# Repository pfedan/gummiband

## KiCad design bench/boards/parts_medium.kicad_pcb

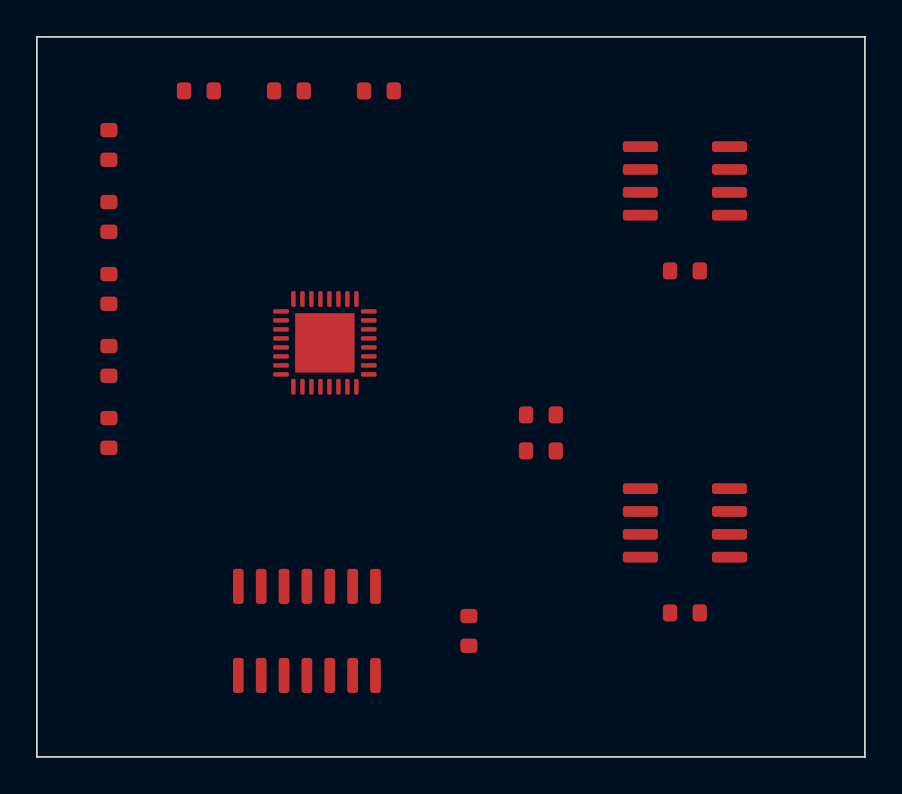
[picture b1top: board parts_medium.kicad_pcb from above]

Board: 2 copper layers, 46.0 x 40.0 mm, 17 parts (0 on the bottom side), 24 nets, no tracks yet.

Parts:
C1, C2, C3: 100n; C_0603
R1, R2: 4k7; R_0603
R3, R4, R5, R6, R7, R8, R9, R10: 10k; R_0603
U1: MCU; QFN-32
U2: Flash; SOIC-8
U3: Sensor; SOIC-8
U4: Latch; SOIC-14

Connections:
+3V3: C1.1, C2.1, C3.1, R1.1, R2.1, U1.25, U2.8, U3.8, U4.14
CS: U1.24, U2.1
GND: C1.2, C2.2, C3.2, U1.33, U2.4, U3.4, U4.7
INT: U1.19, U3.3
MISO: U1.23, U2.2
MOSI: U1.22, U2.5
N1: R5.1, U1.3
N2: R4.1, R6.1
N3: R6.2, R7.2
N4: R5.2, R9.1, U1.4
N5: R3.1, R9.2, U1.8
N6: R8.2, R10.2, U1.28
N7: R4.2, U1.5
N8: R3.2, R8.1, U1.1
N9: R7.1, R10.1, U1.29
Q0: U1.10, U4.13
Q1: U1.11, U4.12
Q2: U1.13, U4.10
Q3: U1.12, U4.11
Q4: U1.14, U4.9
Q5: U1.15, U4.8
SCK: U1.21, U2.6
SCL: R2.2, U1.17, U3.2
SDA: R1.2, U1.18, U3.1

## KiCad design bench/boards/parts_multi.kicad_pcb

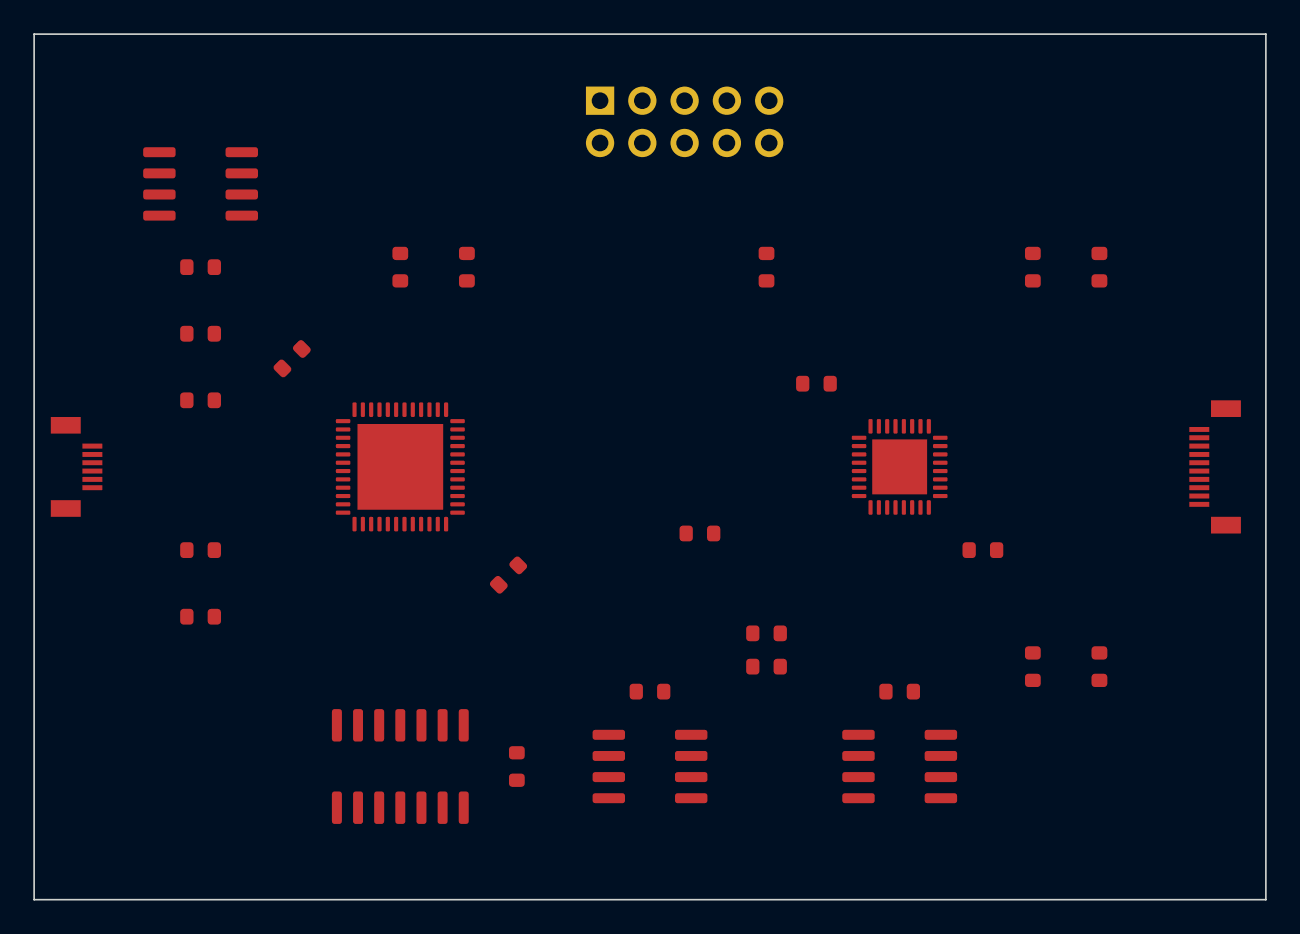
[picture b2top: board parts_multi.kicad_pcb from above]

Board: 4 copper layers, 74.0 x 52.0 mm, 31 parts (0 on the bottom side), 61 nets, no tracks yet.

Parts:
C1, C2, C3, C4, C5, C6, C7, C8: 100n; C_0603
J1: FPC; FPC-6P-0.5mm
J2: FPC; FPC-10P-0.5mm
J3: Conn; PinHeader_2x05
R1, R2: 4k7; R_0603
R3, R4, R5, R6, R7, R8, R9, R10, R11, R12, R13, R14: 10k; R_0603
U1: MCU; QFN-48
U2: MCU; QFN-32
U3: Flash; SOIC-8
U4: Latch; SOIC-14
U5: EEPROM; SOIC-8
U6: Sensor; SOIC-8

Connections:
+3V3: C1.1, C2.1, C3.1, C4.1, C5.1, C6.1, C7.1, C8.1, J3.8, R1.1, R2.1, U1.6, U1.30, U2.1, U3.8, U4.14, U5.8, U6.8
A0: U1.36, U2.2
A1: U1.35, U2.3
A2: U1.34, U2.4
A3: U1.33, U2.5
A4: U1.31, U2.7
A5: U1.32, U2.6
A6: U1.29, U2.8
A7: U1.28, U2.9
CS: U1.25, U2.12
F_CS: U1.46, U3.1
F_MISO: U1.45, U3.2
F_MOSI: U1.44, U3.5
F_SCK: U1.43, U3.6
GND: C1.2, C2.2, C3.2, C4.2, C5.2, C6.2, C7.2, C8.2, J1.1, J1.6, J2.1, J2.4, J2.7, J2.10, J3.6, J3.10, U1.7, U1.49, U2.32, U2.33, U3.4, U4.7, U5.4, U6.4
LED0: J2.5, U2.22
LED1: J2.6, U2.21
N1: R11.2, R12.2
N2: R3.2, R4.2, U1.1
N3: R7.1, R7.2, R8.1
N4: R3.1, R8.2, U3.7
N5: R5.1, U1.42
N6: R4.1, U1.8
N7: R13.2, U2.30, U2.31
N8: R14.1, U1.24, U2.29
N9: R10.2, U2.18
N10: R6.2, U1.13, U4.3
N11: R13.1, U2.13
N12: U1.12, U4.1
N13: R11.1, U2.17
N14: U1.20, U4.5
N15: R14.2, U1.23
N16: U1.38, U3.3
N17: R9.2, R10.1, R12.1
N18: R5.2, R6.1
N19: R9.1, U1.10, U4.4
N20: U1.37, U4.2, U4.6
NRST: J3.5, U1.41
Q0: U1.14, U4.13
Q1: U1.16, U4.11
Q2: U1.15, U4.12
Q3: U1.17, U4.10
Q4: U1.18, U4.9
Q5: U1.19, U4.8
RD: U1.26, U2.11
RX_N: J2.9, U2.19
RX_P: J2.8, U2.20
SCL: R2.2, U1.22, U2.16, U5.6, U6.6
SDA: R1.2, U1.21, U2.15, U5.5, U6.5
SWCLK: J3.3, U1.40
SWDIO: J3.1, U1.39
S_INT: U2.14, U6.1
TCK: J3.9, U2.27
TDI: J3.2, U2.26
TDO: J3.4, U2.25
TMS: J3.7, U2.28
TX_N: J2.3, U2.23
TX_P: J2.2, U2.24
USB_N: J1.3, U1.5
USB_P: J1.4, U1.4
WR: U1.27, U2.10

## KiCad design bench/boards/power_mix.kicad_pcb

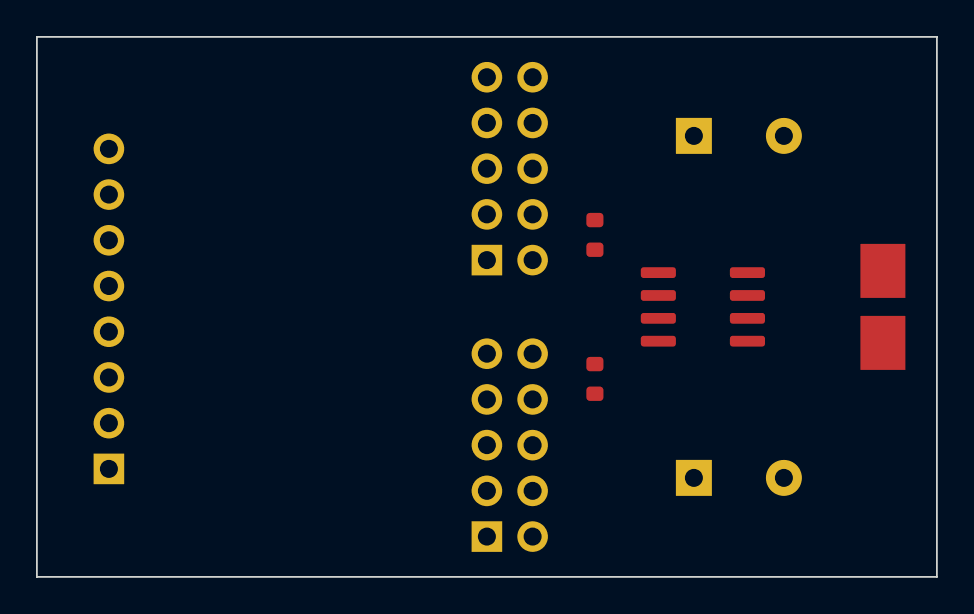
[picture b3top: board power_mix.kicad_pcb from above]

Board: 2 copper layers, 50.0 x 30.0 mm, 9 parts (0 on the bottom side), 7 nets, no tracks yet.

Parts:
C1, C2: 470u; CP_Radial_D8.0mm_P5.00mm
J1: Conn; PinHeader_1x08
J2: Load; PowerTab_2P
J3, J4: NC; PinHeader_2x05
R1, R2: 10k; R_0603
U1: Buck; SOIC-8

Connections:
GND: C1.2, C2.2, J1.3, J1.4, J2.2, R1.2, R2.2, U1.4
S1: J1.5, R1.1, U1.2
S2: J1.6, R2.1, U1.3
S3: J1.7, U1.5
S4: J1.8, U1.6
VIN: C1.1, J1.1, J1.2, U1.1, U1.8
VOUT: C2.1, J2.1, U1.7

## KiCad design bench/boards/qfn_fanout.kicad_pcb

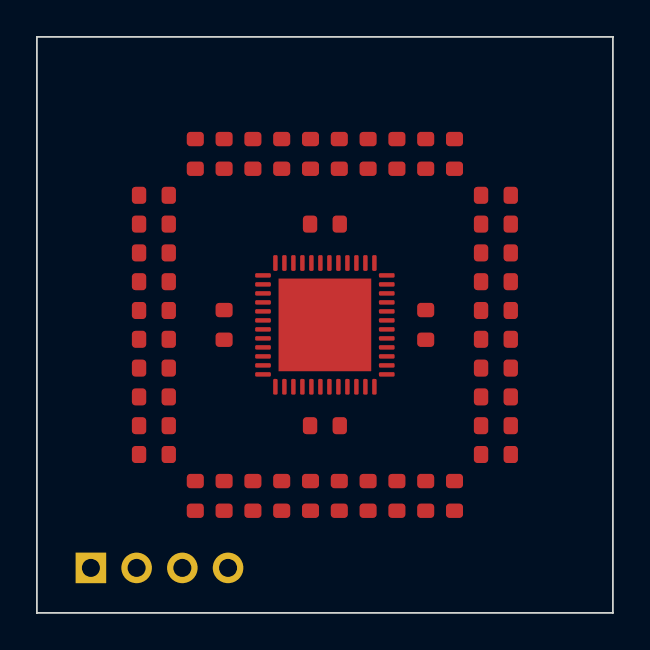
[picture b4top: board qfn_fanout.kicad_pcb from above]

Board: 4 copper layers, 32.0 x 32.0 mm, 46 parts (0 on the bottom side), 44 nets, no tracks yet.

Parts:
C1, C2, C3, C4: 100n; C_0603
J1: Conn; PinHeader_1x04
R1, R2, R3, R4, R5, R6, R7, R8, R9, R10, R11, R12, R13, R14, R15, R16, R17, R18, R19, R20, R21, R22, R23, R24, R25, R26, R27, R28, R29, R30, R31, R32, R33, R34, R35, R36, R37, R38, R39, R40: 10k; R_0603
U1: MCU; QFN-48

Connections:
+3V3: C1.1, C2.1, C3.1, C4.1, J1.2, R2.2, R4.2, R6.2, R8.2, R10.2, R12.2, R14.2, R16.2, R18.2, R20.2, R22.2, R24.2, R26.2, R28.2, R30.2, R32.2, R34.2, R36.2, R38.2, R40.2, U1.6, U1.18, U1.30, U1.42
GND: C1.2, C2.2, C3.2, C4.2, J1.1, R1.2, R3.2, R5.2, R7.2, R9.2, R15.2, R17.2, R19.2, R21.2, R23.2, R25.2, R27.2, R29.2, R31.2, R33.2, R35.2, R37.2, R39.2, U1.7, U1.19, U1.31, U1.43, U1.49
RX: J1.4, R13.2
S1: R1.1, U1.1
S2: R2.1, U1.2
S3: R3.1, U1.3
S4: R4.1, U1.4
S5: R5.1, U1.5
S6: R6.1, U1.8
S7: R7.1, U1.9
S8: R8.1, U1.10
S9: R9.1, U1.11
S10: R10.1, U1.12
S11: R11.1, U1.13
S12: R12.1, U1.14
S13: R13.1, U1.15
S14: R14.1, U1.16
S15: R15.1, U1.17
S16: R16.1, U1.20
S17: R17.1, U1.21
S18: R18.1, U1.22
S19: R19.1, U1.23
S20: R20.1, U1.24
S21: R21.1, U1.36
S22: R22.1, U1.35
S23: R23.1, U1.34
S24: R24.1, U1.33
S25: R25.1, U1.32
S26: R26.1, U1.29
S27: R27.1, U1.28
S28: R28.1, U1.27
S29: R29.1, U1.26
S30: R30.1, U1.25
S31: R31.1, U1.48
S32: R32.1, U1.47
S33: R33.1, U1.46
S34: R34.1, U1.45
S35: R35.1, U1.44
S36: R36.1, U1.41
S37: R37.1, U1.40
S38: R38.1, U1.39
S39: R39.1, U1.38
S40: R40.1, U1.37
TX: J1.3, R11.2

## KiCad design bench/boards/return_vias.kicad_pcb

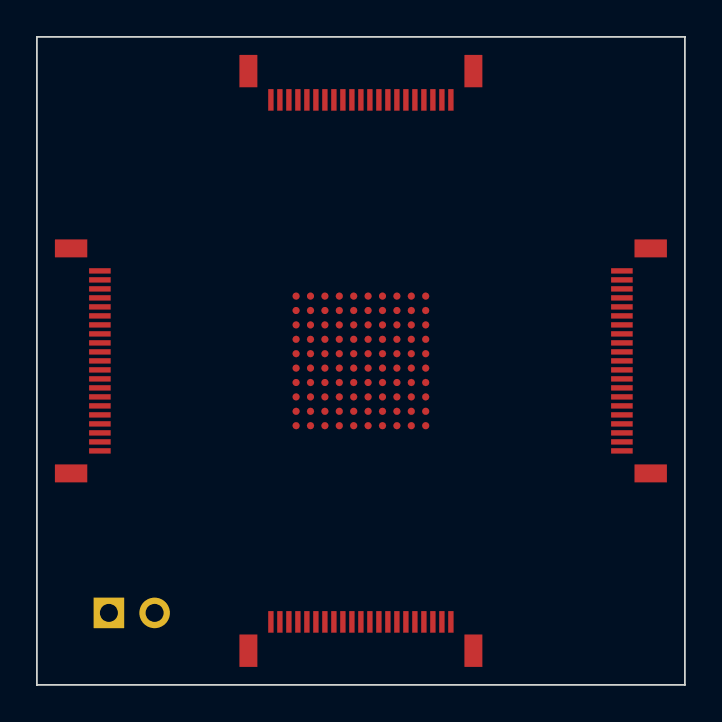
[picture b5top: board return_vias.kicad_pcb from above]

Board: 6 copper layers, 36.0 x 36.0 mm, 6 parts (0 on the bottom side), 85 nets, no tracks yet.

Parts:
J1, J2, J3, J4: FPC; FPC-21P-0.5mm
J5: Conn; PinHeader_1x02
U1: FPGA; BGA-100

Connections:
B0_0: J1.1, U1.A1
B0_1: J1.2, U1.A2
B0_2: J1.3, U1.B2
B0_3: J1.4, U1.A3
B0_4: J1.5, U1.B3
B0_5: J1.6, U1.C3
B0_6: J1.7, U1.A4
B0_7: J1.8, U1.B4
B0_8: J1.9, U1.C4
B0_9: J1.10, U1.A5
B0_10: J1.11, U1.B5
B0_11: J1.12, U1.C5
B0_12: J1.13, U1.A6
B0_13: J1.14, U1.B6
B0_14: J1.15, U1.C6
B0_15: J1.16, U1.A7
B0_16: J1.17, U1.B7
B0_17: J1.18, U1.C7
B0_18: J1.19, U1.A8
B0_19: J1.20, U1.B8
B0_20: J1.21, U1.A9
B1_0: J2.1, U1.A10
B1_1: J2.2, U1.B10
B1_2: J2.3, U1.B9
B1_3: J2.4, U1.C10
B1_4: J2.5, U1.C9
B1_5: J2.6, U1.C8
B1_6: J2.7, U1.D10
B1_7: J2.8, U1.D9
B1_8: J2.9, U1.D8
B1_9: J2.10, U1.E10
B1_10: J2.11, U1.E9
B1_11: J2.12, U1.E8
B1_12: J2.13, U1.F10
B1_13: J2.14, U1.F9
B1_14: J2.15, U1.F8
B1_15: J2.16, U1.G10
B1_16: J2.17, U1.G9
B1_17: J2.18, U1.G8
B1_18: J2.19, U1.H10
B1_19: J2.20, U1.H9
B1_20: J2.21, U1.J10
B2_0: J3.21, U1.K2
B2_1: J3.20, U1.K3
B2_2: J3.19, U1.J3
B2_3: J3.18, U1.K4
B2_4: J3.17, U1.J4
B2_5: J3.16, U1.H4
B2_6: J3.15, U1.K5
B2_7: J3.14, U1.J5
B2_8: J3.13, U1.H5
B2_9: J3.12, U1.K6
B2_10: J3.11, U1.J6
B2_11: J3.10, U1.H6
B2_12: J3.9, U1.K7
B2_13: J3.8, U1.J7
B2_14: J3.7, U1.H7
B2_15: J3.6, U1.K8
B2_16: J3.5, U1.J8
B2_17: J3.4, U1.H8
B2_18: J3.3, U1.K9
B2_19: J3.2, U1.J9
B2_20: J3.1, U1.K10
B3_0: J4.21, U1.B1
B3_1: J4.20, U1.C1
B3_2: J4.19, U1.C2
B3_3: J4.18, U1.D1
B3_4: J4.17, U1.D2
B3_5: J4.16, U1.D3
B3_6: J4.15, U1.E1
B3_7: J4.14, U1.E2
B3_8: J4.13, U1.E3
B3_9: J4.12, U1.F1
B3_10: J4.11, U1.F2
B3_11: J4.10, U1.F3
B3_12: J4.9, U1.G1
B3_13: J4.8, U1.G2
B3_14: J4.7, U1.G3
B3_15: J4.6, U1.H1
B3_16: J4.5, U1.H2
B3_17: J4.4, U1.H3
B3_18: J4.3, U1.J1
B3_19: J4.2, U1.J2
B3_20: J4.1, U1.K1
GND: J5.1, J5.2, U1.D4, U1.D5, U1.D6, U1.D7, U1.E4, U1.E5, U1.E6, U1.E7, U1.F4, U1.F5, U1.F6, U1.F7, U1.G4, U1.G5, U1.G6, U1.G7

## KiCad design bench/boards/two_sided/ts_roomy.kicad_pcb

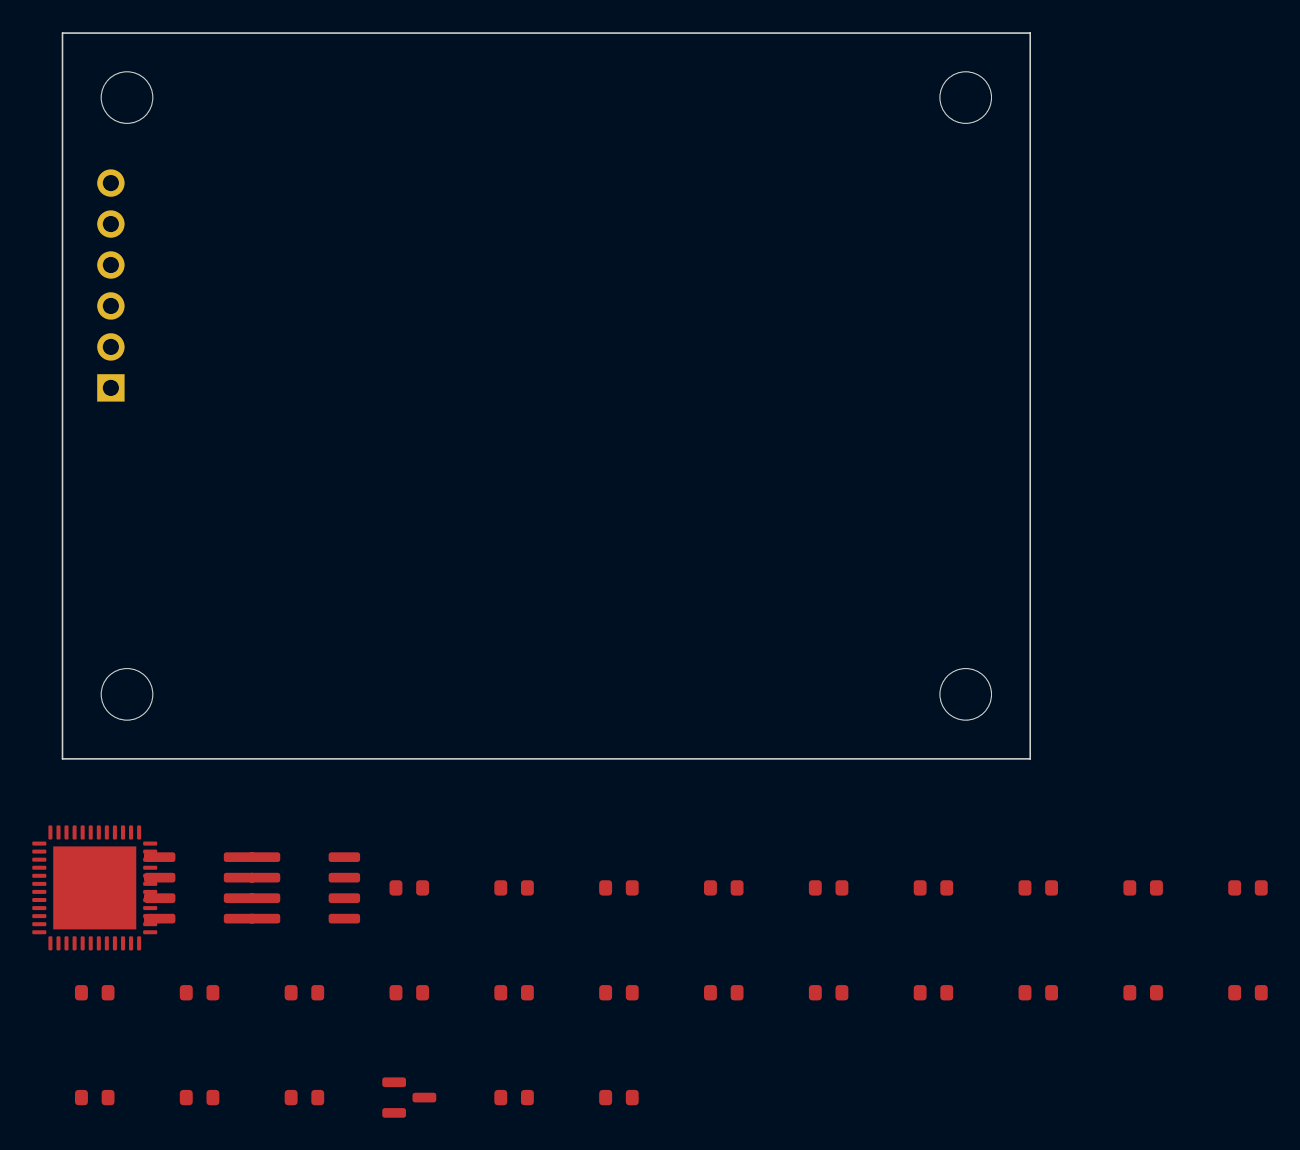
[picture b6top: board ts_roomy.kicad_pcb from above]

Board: 2 copper layers, 60.0 x 45.0 mm, 35 parts (0 on the bottom side), 40 nets, no tracks yet.

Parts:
C1, C2, C3, C4, C5, C6, C7, C8: 100n; C_0603
C20, C21: 10u; C_0603
H1, H2, H3, H4: MH; MountingHole_3.2mm_M3
J1: Conn; PinHeader_1x06
R1, R2, R3, R4, R5, R6, R7, R8, R9, R10, R11, R12, R13, R14, R15, R16: 10k; R_0603
U1: MCU; QFN-48
U2: Flash; SOIC-8
U3: Sensor; SOIC-8
U4: LDO; SOT-23

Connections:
+3V3: C1.1, C2.1, C3.1, C4.1, C5.1, C6.1, C7.1, C8.1, C21.1, U1.6, U1.18, U1.30, U1.42, U2.8, U3.8, U4.3
B0: U1.1, U2.1
B1: U1.2, U2.2
B2: U1.3, U2.3
B3: U1.4, U2.5
B4: U1.5, U2.6
B5: U1.8, U2.7
B6: U1.9, U3.1
B7: U1.10, U3.2
B8: U1.11, U3.3
B9: U1.12, U3.5
B10: U1.13, U3.6
B11: U1.14, U3.7
GND: C1.2, C2.2, C3.2, C4.2, C5.2, C6.2, C7.2, C8.2, C20.2, C21.2, J1.2, U1.7, U1.19, U1.31, U1.43, U1.49, U2.4, U3.4, U4.1
N1: R5.2, R6.2, R7.1
N2: R4.1, R15.2
N3: R11.2, R12.1
N4: R10.1, R11.1
N5: R8.1, R9.2
N6: R3.1, R14.1
N7: R14.2, R15.1, U1.21
N8: R3.2, U1.26
N9: R5.1, U1.23
N10: R2.2, R6.1, U1.39
N11: R7.2, U1.35
N12: R16.1, U1.41
N13: R16.2, U1.25
N14: R12.2, U1.45
N15: R1.1, R4.2
N16: R13.1, U1.48
N17: R10.2, U1.22
N18: R1.2, R9.1, U1.37
N19: R13.2, U1.29
N20: R2.1, U1.47
N21: R8.2, U1.34
RX: J1.4, U1.16
SWC: J1.6, U1.20
SWD: J1.5, U1.17
TX: J1.3, U1.15
VIN: C20.1, J1.1, U4.2
